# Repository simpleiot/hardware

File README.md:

# Simple IoT Hardware

The Simple IoT hardware currently consists of a gateway with a
[Feather](https://learn.adafruit.com/adafruit-feather/) socket that works with
modules from
[Particle](https://store.particle.io/collections/prototyping-hardware) and
[Adafruit](https://www.adafruit.com/feather). Multiple sensor/IO nodes can be
attach to the gateway and daisychained for 10's of feet. The system is
waterproof and uses low cost
[xConnect](https://www.wiredwatts.com/3-core-xconnect-connector) 3-wire
connectors.

## Software

The Simple IoT project also includes open source gateway
[firmware](https://github.com/simpleiot/firmware/tree/master/siot-fw) and
[portal](https://github.com/simpleiot/simpleiot) software.

## Gateway

- [Feather](https://learn.adafruit.com/adafruit-feather/) socket
- Two 3-wire expansion pigtails (power, 1-wire, data)
- Power (5-24VDC) can be attached to either expansion connector
- Sensors can be attached to both expansion connectors
- Waterproof, UV resistant enclosure
- [design files](https://github.com/simpleiot/hardware/tree/master/siot-gateway-particle)

## Temperature node

- two DS18B20 1-wire temperature sensors
- [design files](https://github.com/simpleiot/hardware/tree/master/siot-node-temp)

## AC Current measurement node

- uses [CR9580](https://www.crmagnetics.com/current-sensors/cr9580) current
  sensors
- [design files](https://github.com/simpleiot/hardware/tree/master/siot-node-current-clamp)

## Relay node

- 5A Relay
  ([G6DN-1A-L-DC5](https://www.mouser.com/datasheet/2/307/en-g6dn-838135.pdf))
- [design files](https://github.com/simpleiot/hardware/tree/master/siot-node-relay)

The relay node has a terminal block inside the enclosure. The above example
shows an example of an AC plug switched by the relay. Although the relay is
rated for line level voltages, the PCB design is not UL tested or certified for
line level voltages, so use at your own risk.

## Sensor extension cables

xConnect extension cables can be purchased from
[Wired Watts](https://www.wiredwatts.com/3-core-xconnect-connector)

## Pull Requests Welcome

This is a community project -- pull requests will be considered.

## License

Apache Version 2.0

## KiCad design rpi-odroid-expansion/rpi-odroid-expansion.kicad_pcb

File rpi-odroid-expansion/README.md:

# rPI/Odroid Exansion Board

## Features

This board is designed to provide a number of expansion features to Raspberry PI
and ODROID-C4 SBCs.

- CAN
- RS485
- 1-wire
- LCD/Touchscreen
- pass through rPI expansion connector to provide use of unused pins.
- XBee socket (Digi, Nimbelink, etc radios)
  - reference design: https://nimbelink.com/products/raspberry-pi-skywire-adapter/
  - supports both standard 40-pin expansion and compute module
- LoraWan radio

## MPU Interface

- [rPI4 pinout](https://www.raspberrypi.org/documentation/hardware/raspberrypi/schematics/README.md)
- [ODROID-C4 pinout](https://wiki.odroid.com/odroid-c4/hardware/expansion_connectors)

## MPU/MCU communication link

There is a UART and SPI ports (todo) wired between the host MPU and the MCU on
the expansion board.

- UART is likely simplest as the existing CAN firmware implements a USB serial
  port. Also, for RS485, it is just a pass through.
- SPI would allow us to run both CAN and RS485 at the same time.
- may only be two hardware SPI chip selects, so not sure how well more than 2
  SPI devices will work.

## MCU Implementation

A STM32F042K4Tx MCU is used to implement the following functionality:

- CAN Interface
- Board ID EEPROM (implements i2c slave)

Reference

- [ST Web Site](https://www.st.com/en/microcontrollers-microprocessors/stm32f042k4.html)
- [Datasheet](https://www.st.com/resource/en/datasheet/stm32f042k4.pdf)
- [Reference manual](https://www.st.com/resource/en/reference_manual/dm00031936-stm32f0x1stm32f0x2stm32f0x8-advanced-armbased-32bit-mcus-stmicroelectronics.pdf)
- [Programming manual](https://www.st.com/resource/en/programming_manual/dm00051352-stm32f0xxx-cortexm0-programming-manual-stmicroelectronics.pdf)

### CAN

Can is typically implemented using a SPI CAN controller (ex MCP2517), but these
devices do not offer any buffering so are a poor choice for non real-time
operating systems like Linux. Thus, we've chosen to use a MCU to provide the CAN
interface and hopefully leverage firmware from the following projects:

- https://github.com/linklayer/cantact-hw
- https://github.com/normaldotcom/candleLight_fw
- SLCAN

### HAT ID EEPROM

### RS485

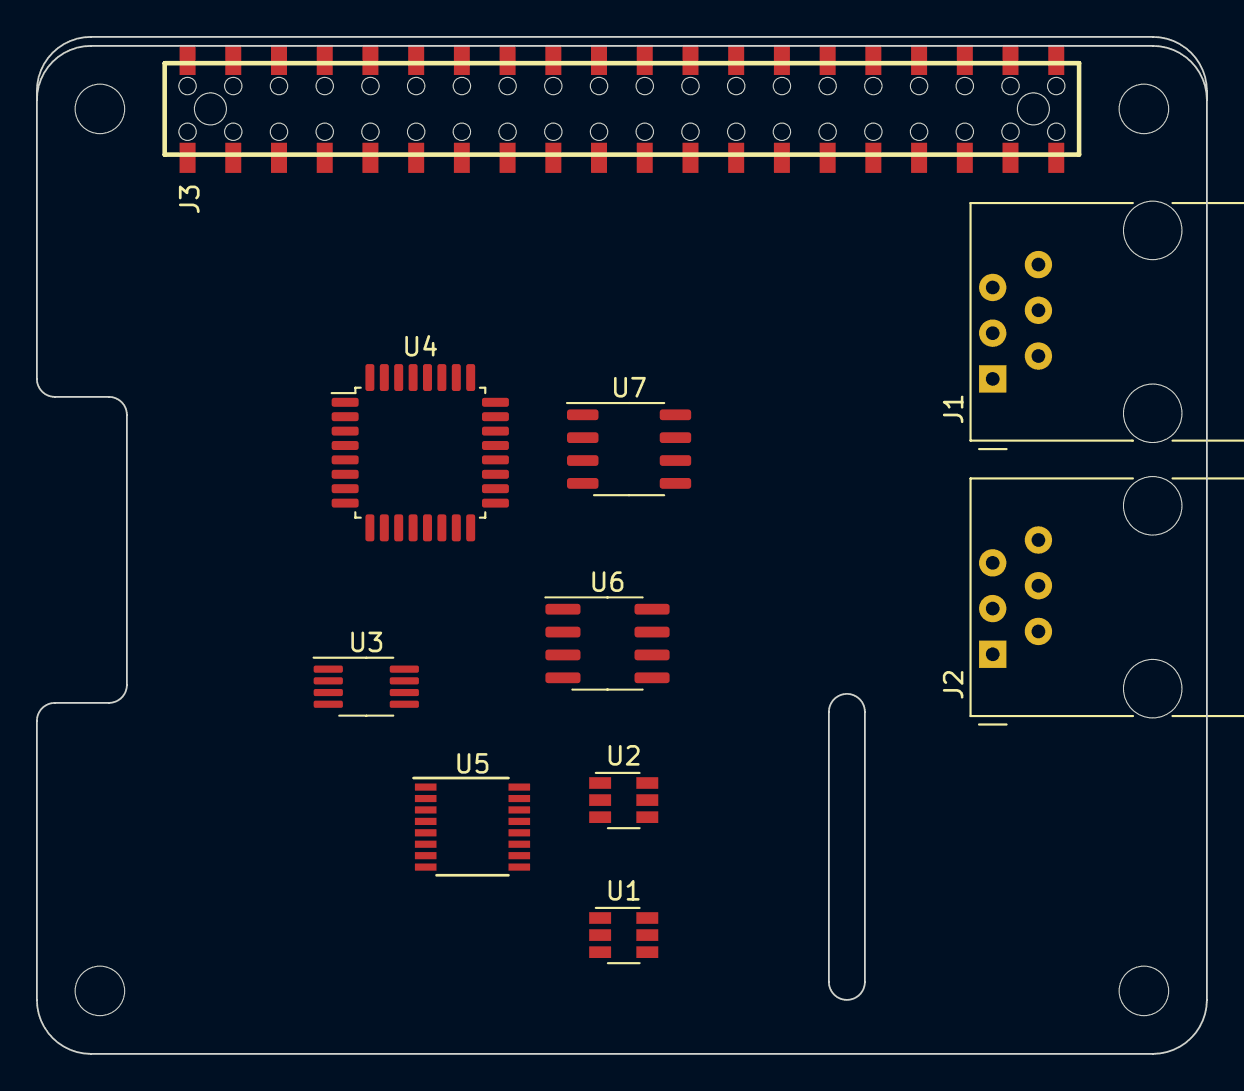
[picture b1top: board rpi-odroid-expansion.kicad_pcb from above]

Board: 2 copper layers, 65.0 x 56.5 mm, 10 parts (0 on the bottom side), 22 nets, no tracks yet.

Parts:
J1, J2: RJ9; RJ12_Amphenol_54601
J3: rPI_02x20; Samtec_HLE-120-02-XXX-DV-BE-XX-XX
U1, U2: DS2484R; TSOT-23-6
U3: PCF8563TS; MSOP-8_3x3mm_P0.65mm
U4: STM32F042K4T6; LQFP-32_7x7mm_P0.8mm
U5: TSC2046; SSOP-16_3.9x4.9mm_P0.635mm
U6: MCP2551-I-SN; SOIC-8_3.9x4.9mm_P1.27mm
U7: MAX13487E; SO-8_3.9x4.9mm_P1.27mm

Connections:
+3V3: J3.1, J3.17, U4.1, U4.5, U4.17, U5.1, U5.10, U7.2, U7.3
+5V: J1.4, J2.4, J3.2, J3.4, U1.6, U2.6, U6.3, U7.8
/CAN_RX: U4.21, U6.4
/CAN_TX: U4.22, U6.1
/GPIO5: J3.29, U4.28
/I2C_SCL: J3.5, U1.3, U2.3, U3.6
/I2C_SDA: J3.3, U1.2, U2.2, U3.5
/ID_SCL: J3.28, U4.29
/ID_SDA: J3.27, U4.30
/MCU_RSTn: J3.36, U4.4
/RS485_RX: U4.20, U7.1
/RS485_TX: U4.19, U7.4
/SPI_CLK: J3.23, U4.11, U5.16
/SPI_CS1: J3.26, U5.15
/SPI_MISO: J3.21, U4.13, U5.12
/SPI_MOSI: J3.19, U4.12, U5.14
/UART_RX: J3.10, U4.8
/UART_TX: J3.8, U4.9
/W1_A: J1.2, U1.5
/W1_B: J2.2, U2.5
/W1_BUSA: J3.7, U1.1, U2.1
GND: J1.1, J1.3, J2.1, J2.3, J3.6, J3.9, J3.14, J3.20, J3.25, J3.30, J3.34, J3.39, U1.4, U2.4, U3.4, U4.16, U4.32, U5.6, U6.2, U6.8, U7.5

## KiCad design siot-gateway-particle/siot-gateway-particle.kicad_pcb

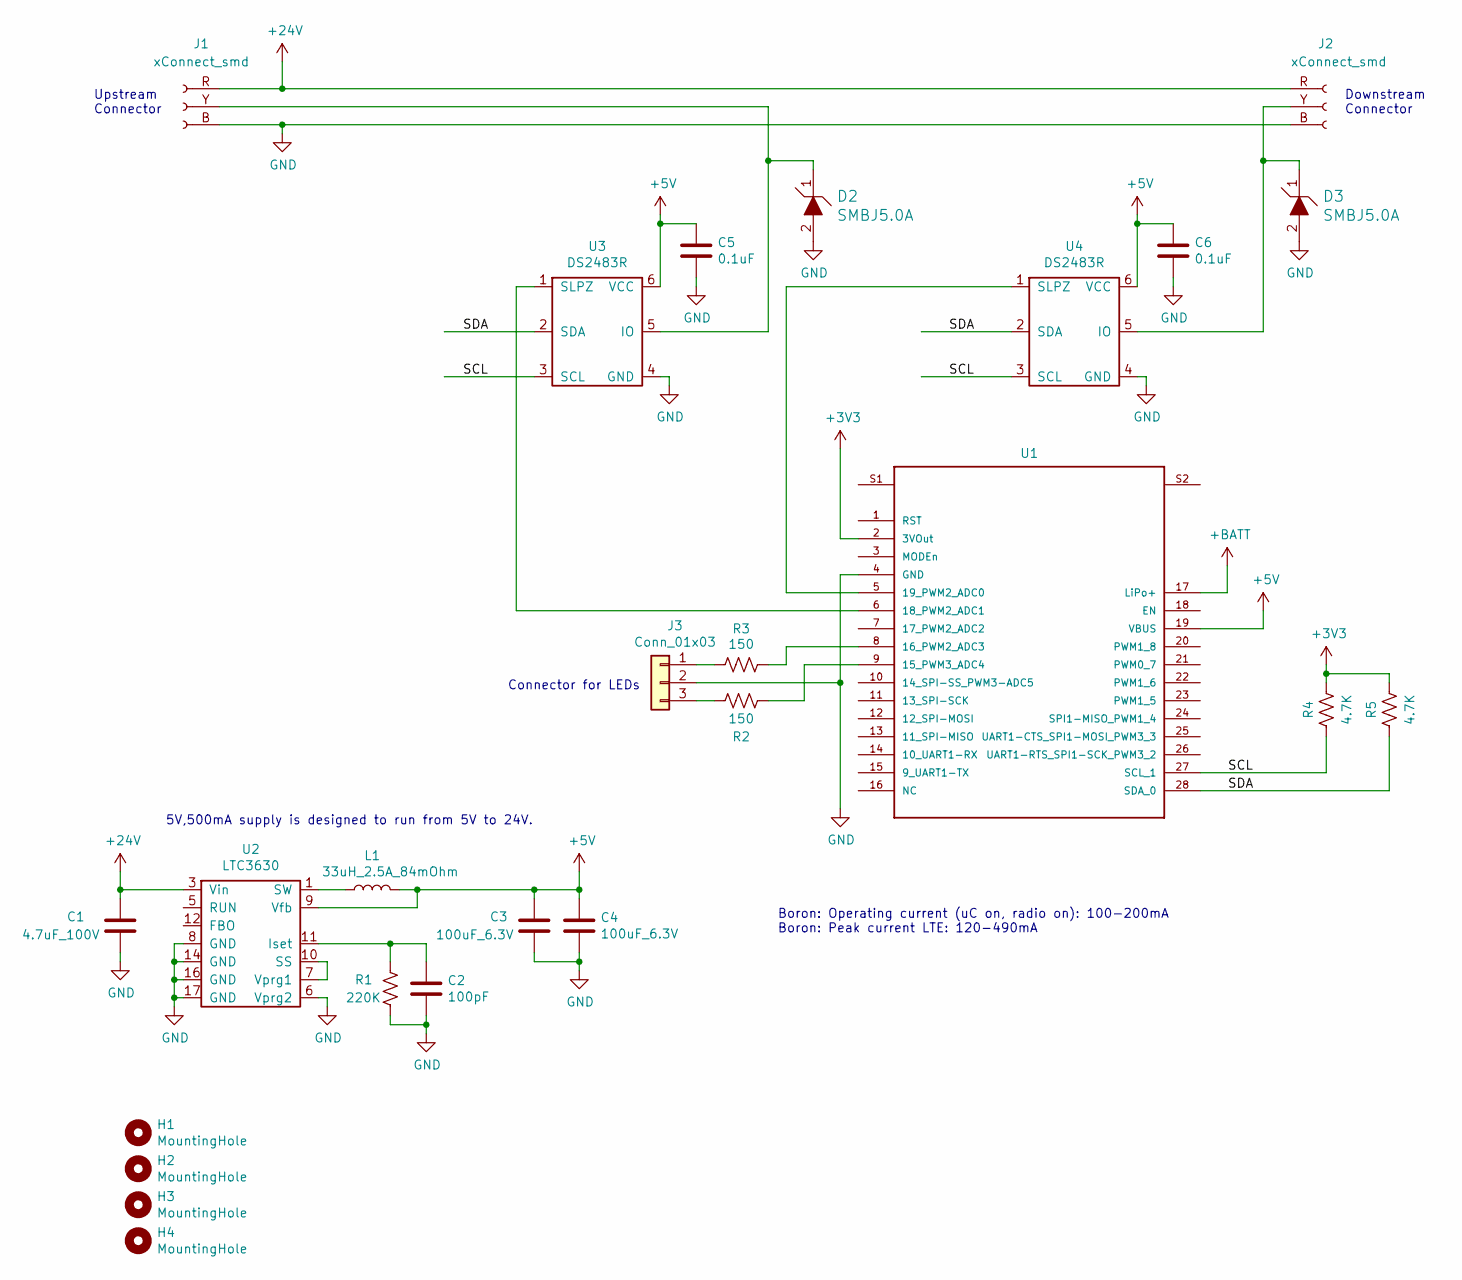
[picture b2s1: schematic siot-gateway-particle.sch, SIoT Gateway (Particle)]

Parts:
C1: 4.7uF_100V; C_2220_5650Metric; MPN C5750X7R2A475M230KA
C2: 100pF; C_0603_1608Metric
C3, C4: 100uF_6.3V; C_1210_3225Metric; MPN 12106D107MAT2A
C5, C6: 0.1uF; C_0603_1608Metric
D2, D3: SMBJ5.0A; D_SMB; MPN SMBJ5.0A
H1, H2, H3, H4: MountingHole; MountingHole_3.5mm
J1, J2: xConnect_smd
J3: Conn_01x03; PinHeader_1x03_P2.54mm_Vertical
L1: 33uH_2.5A_84mOhm; CDRH105R; MPN CDRH105RNP-330NC
R1: 220K; R_0603_1608Metric
R2, R3: 150; R_0603_1608Metric
R4, R5: 4.7K; R_0603_1608Metric
U1: Particle_Mesh; feather
U2: LTC3630; MSOP-12-16-1EP_3x4mm_P0.5mm_EP1.65x2.85mm_ThermalVias; MPN LTC3630EMSE#PBF
U3, U4: DS2483R; TSOT-23-6; MPN DS2483R+T

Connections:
+3V3: R4.2, R5.2, U1.2 (3VOut)
+5V: C3.1, C4.1, C5.1, C6.1, L1.2, U1.19 (VBUS), U2.9 (Vfb), U3.6 (VCC), U4.6 (VCC)
+24V: C1.1, J1.R (Pin_1), J2.R (Pin_1), U2.3 (Vin)
+BATT: U1.17 (LiPo+)
/SCL: R4.1, U1.27 (SCL_1), U3.3 (SCL), U4.3 (SCL)
/SDA: R5.1, U1.28 (SDA_0), U3.2 (SDA), U4.2 (SDA)
GND: C1.2, C2.2, C3.2, C4.2, C5.2, C6.2, D2.2, D3.2, J1.B (Pin_3), J2.B (Pin_3), J3.2, R1.2, U1.4 (GND), U2.6 (Vprg2), U2.8 (GND), U2.14 (GND), U2.16 (GND), U2.17 (GND), U3.4 (GND), U4.4 (GND)
unnamed: C2.1, R1.1, U2.11 (Iset)
unnamed: D2.1, J1.Y (Pin_2), U3.5 (IO)
unnamed: D3.1, J2.Y (Pin_2), U4.5 (IO)
unnamed: J3.1, R2.2
unnamed: J3.3, R3.2
unnamed: L1.1, U2.1 (SW)
unnamed: R2.1, U1.8 (16_PWM2_ADC3)
unnamed: R3.1, U1.9 (15_PWM3_ADC4)
unnamed: U1.5 (19_PWM2_ADC0), U4.1 (SLPZ)
unnamed: U1.6 (18_PWM2_ADC1), U3.1 (SLPZ)
unnamed: U2.7 (Vprg1), U2.10 (SS)

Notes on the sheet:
Upstream Connector
Downstream Connector
5V,500mA supply is designed to run from 5V to 24V.
Connector for LEDs
Boron: Operating current (uC on, radio on): 100-200mA Boron: Peak current LTE: 120-490mA

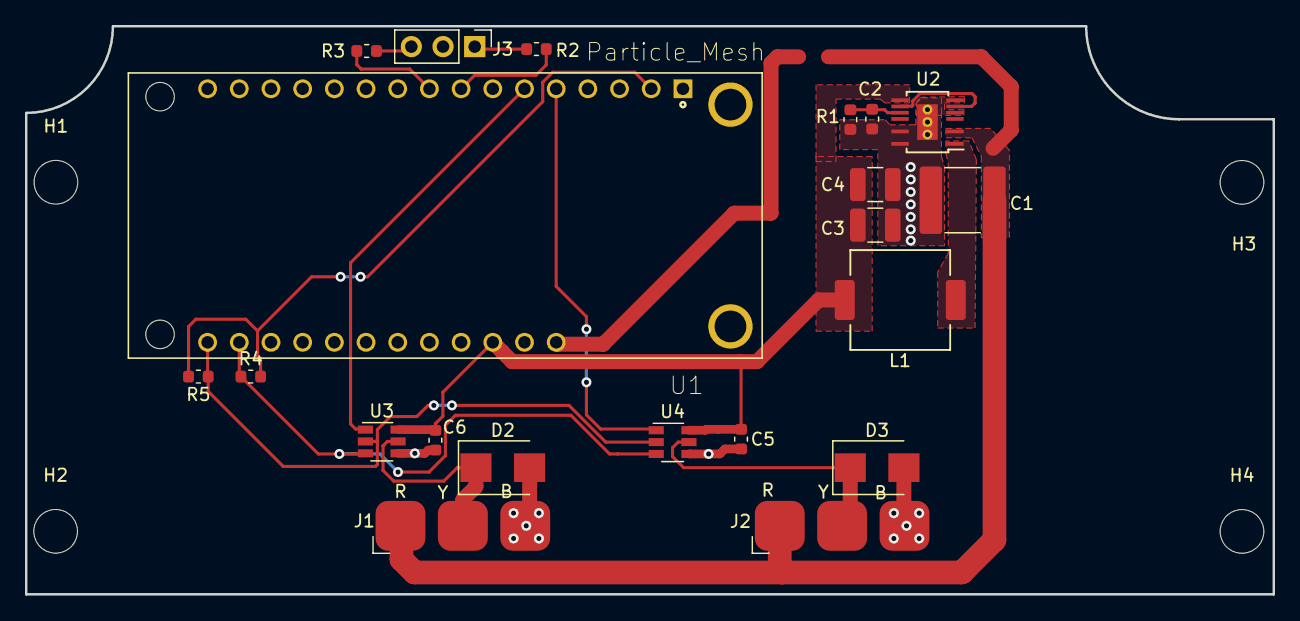
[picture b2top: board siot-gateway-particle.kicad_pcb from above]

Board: 2 copper layers, 100.0 x 45.5 mm, 25 parts (0 on the bottom side), 17 nets.

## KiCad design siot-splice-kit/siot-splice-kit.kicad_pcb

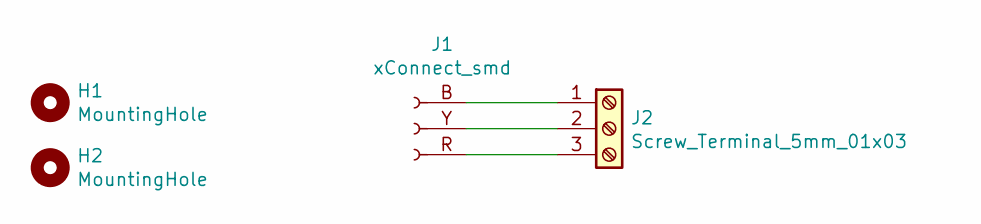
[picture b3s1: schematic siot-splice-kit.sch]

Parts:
H1, H2: MountingHole; MountingHole_3.5mm
J1: xConnect_smd
J2: Screw_Terminal_5mm_01x03; TerminalBlock_Phoenix_PT-1,5-3-5.0-H_1x03_P5.00mm_Horizontal; MPN 1935174

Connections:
unnamed: J1.B (Pin_3), J2.1
unnamed: J1.R (Pin_1), J2.3
unnamed: J1.Y (Pin_2), J2.2

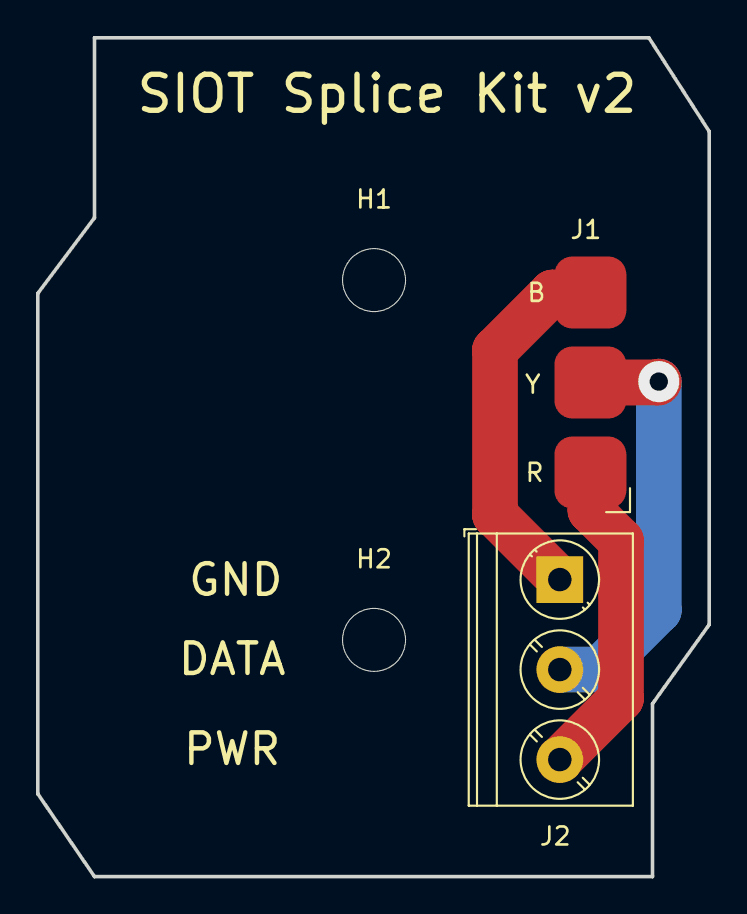
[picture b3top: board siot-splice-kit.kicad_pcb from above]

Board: 2 copper layers, 37.3 x 46.6 mm, 4 parts (0 on the bottom side), 3 nets.

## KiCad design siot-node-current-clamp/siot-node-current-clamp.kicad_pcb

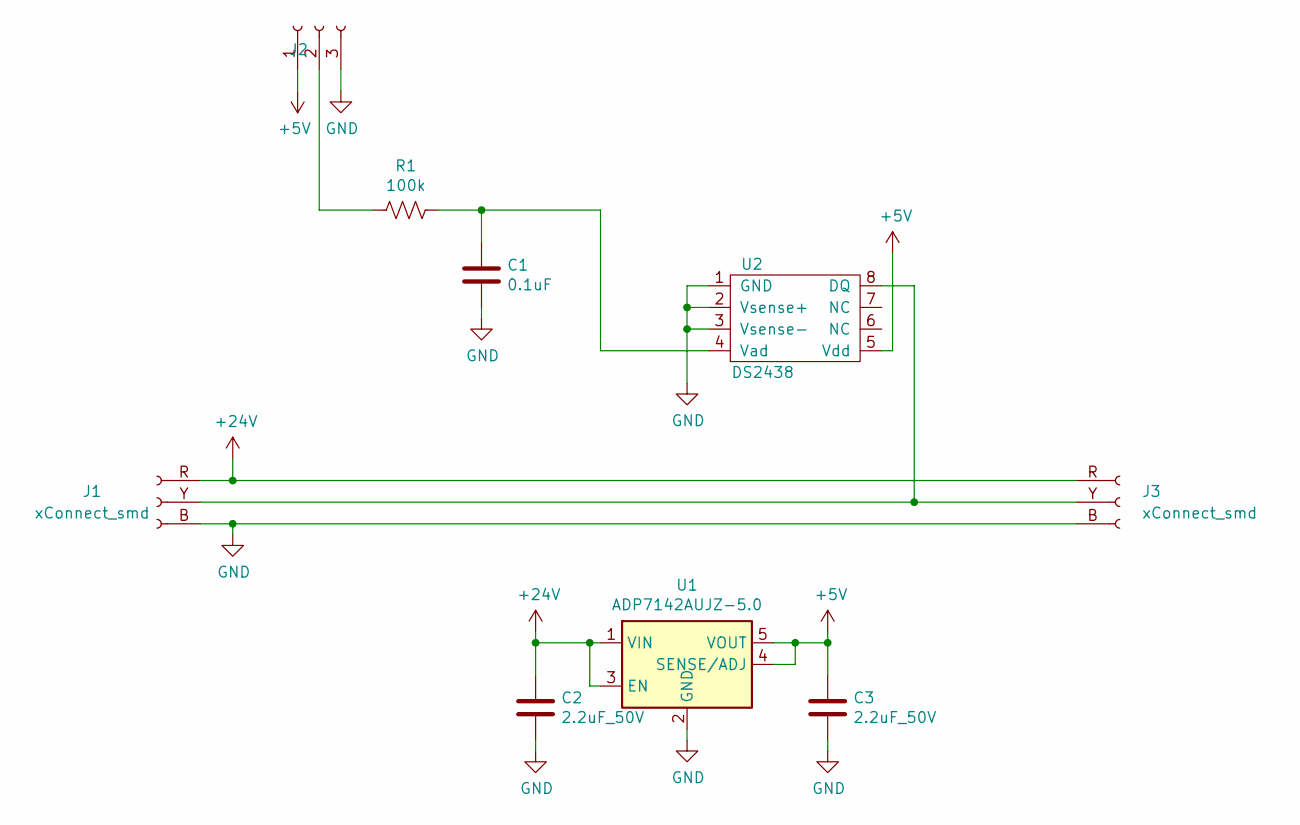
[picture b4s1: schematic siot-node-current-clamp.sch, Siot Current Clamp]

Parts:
C1: 0.1uF; C_0603_1608Metric
C2, C3: 2.2uF_50V; C_0603_1608Metric; MPN GRM188R61H225ME11J
J1, J3: xConnect_smd
J2: Conn_01x02_Female; 1x03_solder-pads
R1: 100k; R_0603_1608Metric
U1: ADP7142AUJZ-5.0; TSOT-23-5; MPN ADP7142AUJZ-5.0
U2: DS2438; SOIC-8_3.9x4.9mm_P1.27mm

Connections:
+5V: C3.1, J2.1, U1.4 (SENSE/ADJ), U1.5 (VOUT), U2.5 (Vdd)
+24V: C2.1, J1.R (Pin_1), J3.R (Pin_1), U1.1 (VIN), U1.3 (EN)
GND: C1.2, C2.2, C3.2, J1.B (Pin_3), J2.3, J3.B (Pin_3), U1.2 (GND), U2.1 (GND), U2.2 (Vsense+), U2.3 (Vsense-)
unnamed: C1.1, R1.1, U2.4 (Vad)
unnamed: J1.Y (Pin_2), J3.Y (Pin_2), U2.8 (DQ)
unnamed: J2.2, R1.2

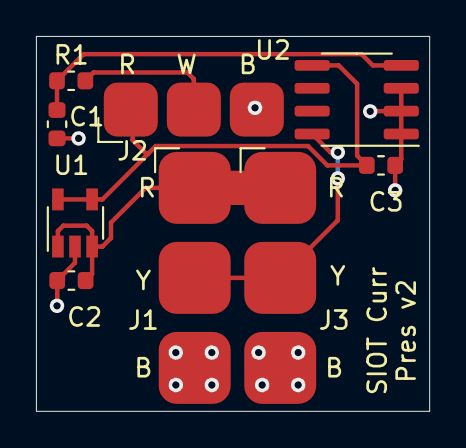
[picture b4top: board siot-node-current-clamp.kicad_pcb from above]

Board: 2 copper layers, 21.8 x 20.8 mm, 9 parts (0 on the bottom side), 6 nets.

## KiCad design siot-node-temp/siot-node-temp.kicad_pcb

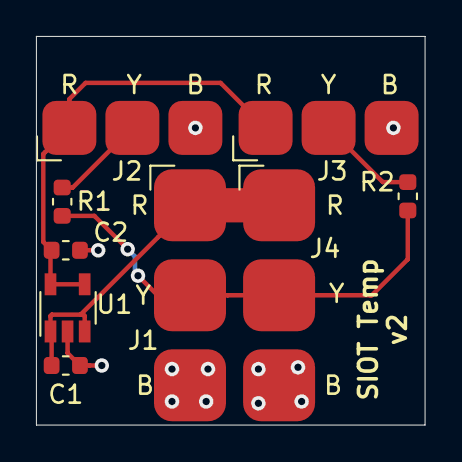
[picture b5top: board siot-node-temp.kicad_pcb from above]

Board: 2 copper layers, 21.6 x 21.6 mm, 9 parts (0 on the bottom side), 6 nets.

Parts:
C1, C2: 2.2uF_50V; C_0603_1608Metric
J1, J4: xConnect_smd
J2, J3: Conn_01x03; 1x03_solder-pads
R1, R2: 1K; R_0603_1608Metric
U1: ADP7142AUJZ-3.3; TSOT-23-5

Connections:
+3V3: C2.1, J2.1, J3.1, U1.4, U1.5
+24V: C1.1, J1.R, J4.R, U1.1, U1.3
/data: J1.Y, J4.Y, R1.2, R2.2
GND: C1.2, C2.2, J1.B, J2.3, J3.3, J4.B, U1.2
unnamed: J2.2, R1.1
unnamed: J3.2, R2.1

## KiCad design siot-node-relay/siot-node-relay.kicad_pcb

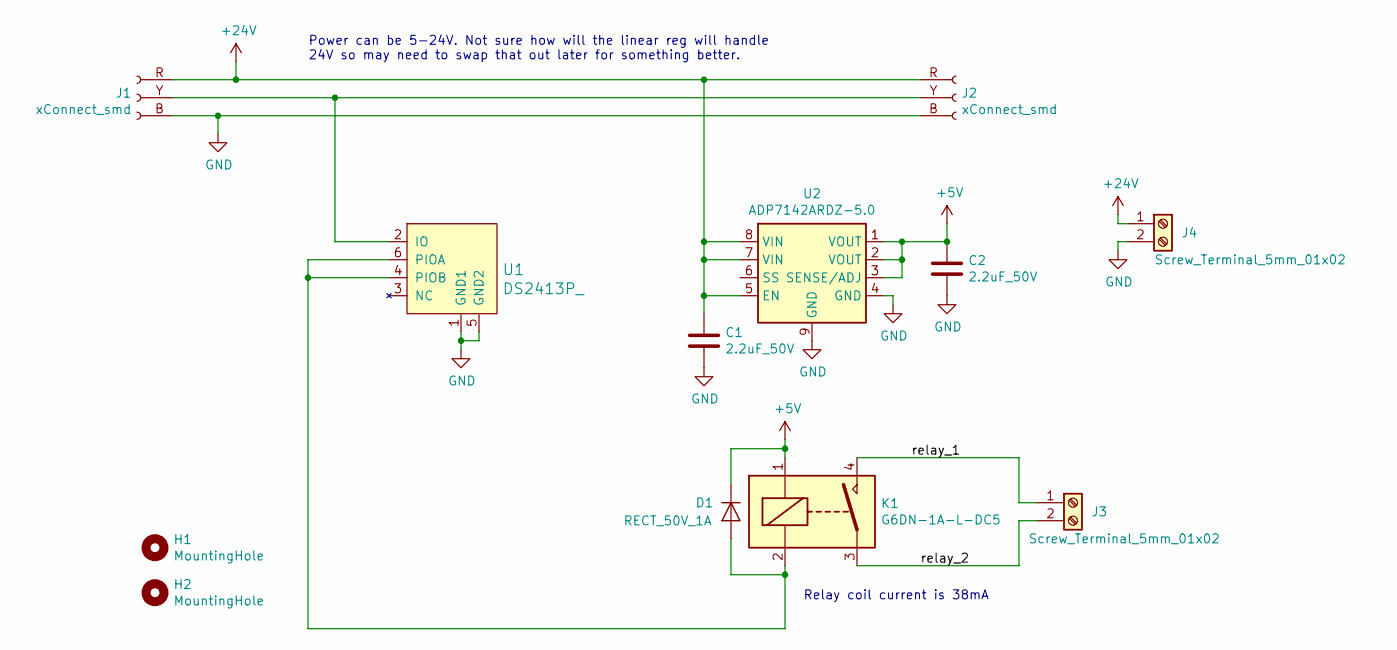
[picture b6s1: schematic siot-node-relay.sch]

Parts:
C1, C2: 2.2uF_50V; C_0603_1608Metric; MPN GRM188R61H225ME11J
D1: RECT_50V_1A; D_SMA; MPN US1M-13-F
H1, H2: MountingHole; MountingHole_3.5mm
J1, J2: xConnect_smd
J3, J4: Screw_Terminal_5mm_01x02; TerminalBlock_Phoenix_PT-1,5-2-5.0-H_1x02_P5.00mm_Horizontal; MPN 1935161
K1: G6DN-1A-L-DC5; OMRON-G6DN-1A-L; MPN G6DN-1A-L DC5
U1: DS2413P_; LSOJ-6_W3.76mm; MPN DS2413P+; Digi-Key_PN DS2413P+-ND
U2: ADP7142ARDZ-5.0; SOIC-8-1EP_3.9x4.9mm_P1.27mm_EP2.29x3mm_ThermalVias; MPN ADP7142ARDZ-5.0

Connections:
+5V: C2.1, D1.1 (K), K1.1, U2.1 (VOUT), U2.2 (VOUT), U2.3 (SENSE/ADJ)
+24V: C1.1, J1.R (Pin_1), J2.R (Pin_1), J4.1, U2.5 (EN), U2.7 (VIN), U2.8 (VIN)
/relay_1: J3.1, K1.4
/relay_2: J3.2, K1.3
GND: C1.2, C2.2, J1.B (Pin_3), J2.B (Pin_3), J4.2, U1.1 (GND1), U1.5 (GND2), U2.4 (GND), U2.9 (GND)
unnamed: D1.2 (A), K1.2, U1.4 (PIOB), U1.6 (PIOA)
unnamed: J1.Y (Pin_2), J2.Y (Pin_2), U1.2 (IO)

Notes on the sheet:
Relay coil current is 38mA
Power can be 5-24V. Not sure how will the linear reg will handle 24V so may need to swap that out later for something better.

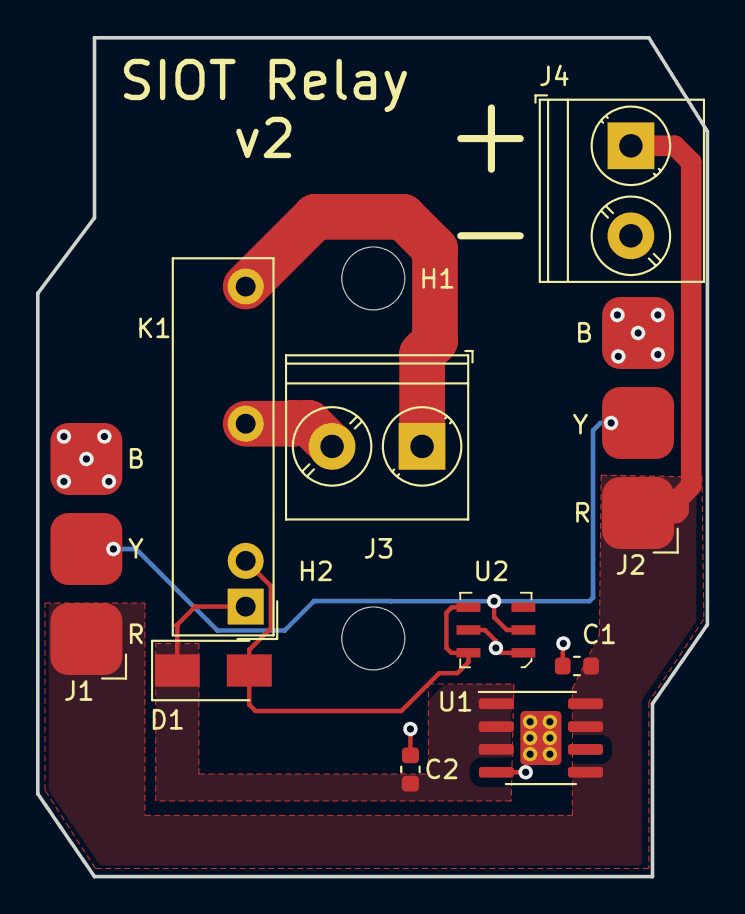
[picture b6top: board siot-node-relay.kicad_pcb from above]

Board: 2 copper layers, 37.2 x 46.6 mm, 12 parts (0 on the bottom side), 7 nets.

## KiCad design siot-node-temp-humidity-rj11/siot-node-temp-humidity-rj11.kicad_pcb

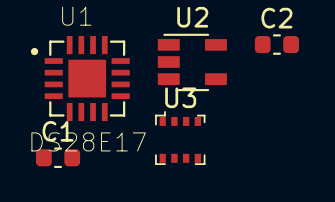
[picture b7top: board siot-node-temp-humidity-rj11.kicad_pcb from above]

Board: 2 copper layers, 5 parts (0 on the bottom side), 6 nets, no tracks yet.

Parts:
C1, C2: 2.2uF_50V; C_0603_1608Metric
U1: DS28E17; QFN65P400X400X80-17N
U2: ADP7142AUJZ-3.3; TSOT-23-5
U3: BME280; Pressure_Sensor_LGA-8_2.5x2.5mm_BME280

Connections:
+3V3: C2.1, U1.6, U2.4, U2.5
+5V: C1.1, U2.1, U2.3
/data: U1.2, U1.3
GND: C1.2, C2.2, U1.4, U1.8, U1.17, U2.2, U3.1, U3.7
unnamed: U1.15, U3.4
unnamed: U1.16, U3.3

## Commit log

2013-10-16 not schematic format
2013-10-16 initial schematic
2019-07-19 start of bec-passive lib
2019-07-19 remove unused project
2019-07-19 add gitignore
2019-07-19 remove backup file
2019-07-19 first pass at temp node
2019-07-19 add pdf
2019-07-19 add pdfs
2019-07-19 fix silkscreen
2019-08-01 add analog lib
2019-08-09 add current clamp design
2019-08-09 add footprint for xConnect pigtail
2019-08-09 fix hole sizes
2019-08-21 add ignore
2019-08-21 add feather footprint
2019-08-21 work on particle symbol
2019-08-21 start of GW schematic
2019-08-24 1st pass of gw finished
2019-08-24 work on SMD xConnect connections
2019-08-27 start of shottkey diode
2019-08-27 library updates
2019-08-27 design updates
2019-09-09 add BOM generation scripts
2019-09-09 update PNs on symbols
2019-09-21 fix missing en on temp board
2019-09-21 fix missing route
2019-09-21 remove temp file
2019-09-21 start of GW design with IO onboard
2019-09-21 remote project that does not belong in this repo
2019-10-17 lib updates
2019-10-17 create relay node design
2019-10-30 add splice kit design
2019-10-30 temp node tweaks
2019-10-30 redo relay node
2019-10-30 GW tweaks
2019-11-01 updates for relay/splice kit
2019-11-01 add rj11 dry contact node
2019-11-01 add temp/humidity node
2019-11-01 add rj11 temp node
2020-01-07 modify script to generate KiCad BOM
2020-06-09 update docs
2020-06-09 set width
2020-06-09 fix image resize
2020-06-09 more resizing
2020-06-09 add gw-internals photo
2020-06-09 add note about relay node
2020-06-09 clean up connector statement
2020-06-09 gramar fix
2020-06-09 add license info
2020-06-09 add PCB screenshots
2020-06-09 add missing paren
2020-06-24 work on documentation
2020-09-23 start rpi-odroid-expansion project
2020-09-23 update libs
2020-09-23 start of gw doc
2020-09-23 start of gateway changes
2020-09-23 ignore rescue and pyc files
2020-09-23 work on gw with IO
2020-09-23 add pdf of schematic
2020-09-28 add 2032 bat holder
2020-09-28 add max rs485 transceiver
2020-09-28 progress on board
2020-09-28 add more notes
2020-09-28 add markdown formatting
2020-09-28 more notes/documentation
2020-09-28 more notes and design tweaks
2020-10-01 add more ideas on requirements
2020-10-12 update parts for rPI expansion project
2020-10-12 fill in pn's, pull in rPI hat outline, etc
2020-10-15 add notes about NL reference design
